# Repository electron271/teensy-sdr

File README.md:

# teensy-sdr
SDR (Software Defined Radio) using a Teensy development board.

## Libraries
https://github.com/XenGi/teensy_library
https://github.com/XenGi/teensy.pretty

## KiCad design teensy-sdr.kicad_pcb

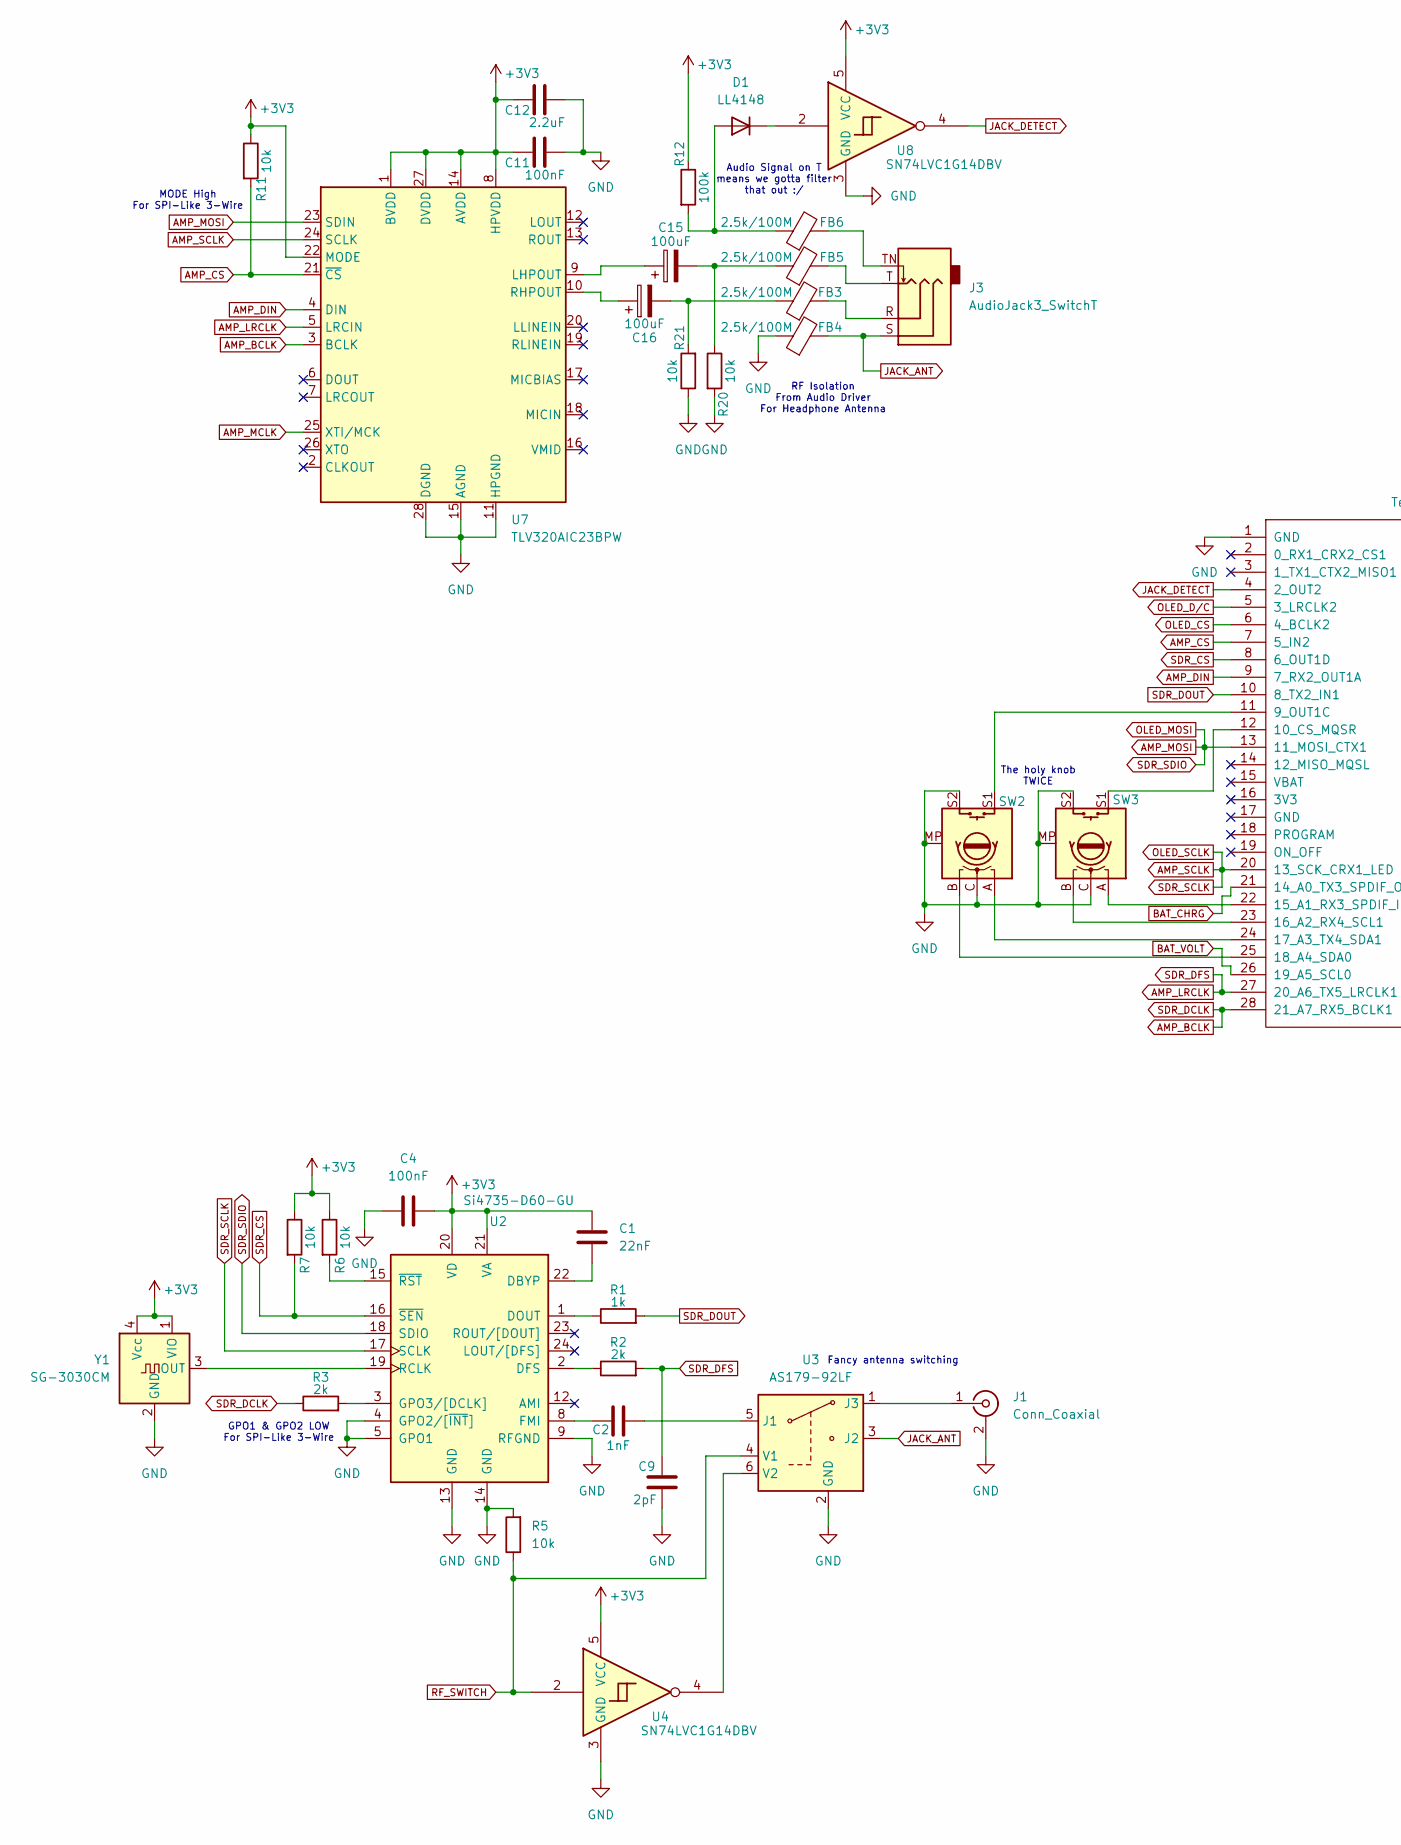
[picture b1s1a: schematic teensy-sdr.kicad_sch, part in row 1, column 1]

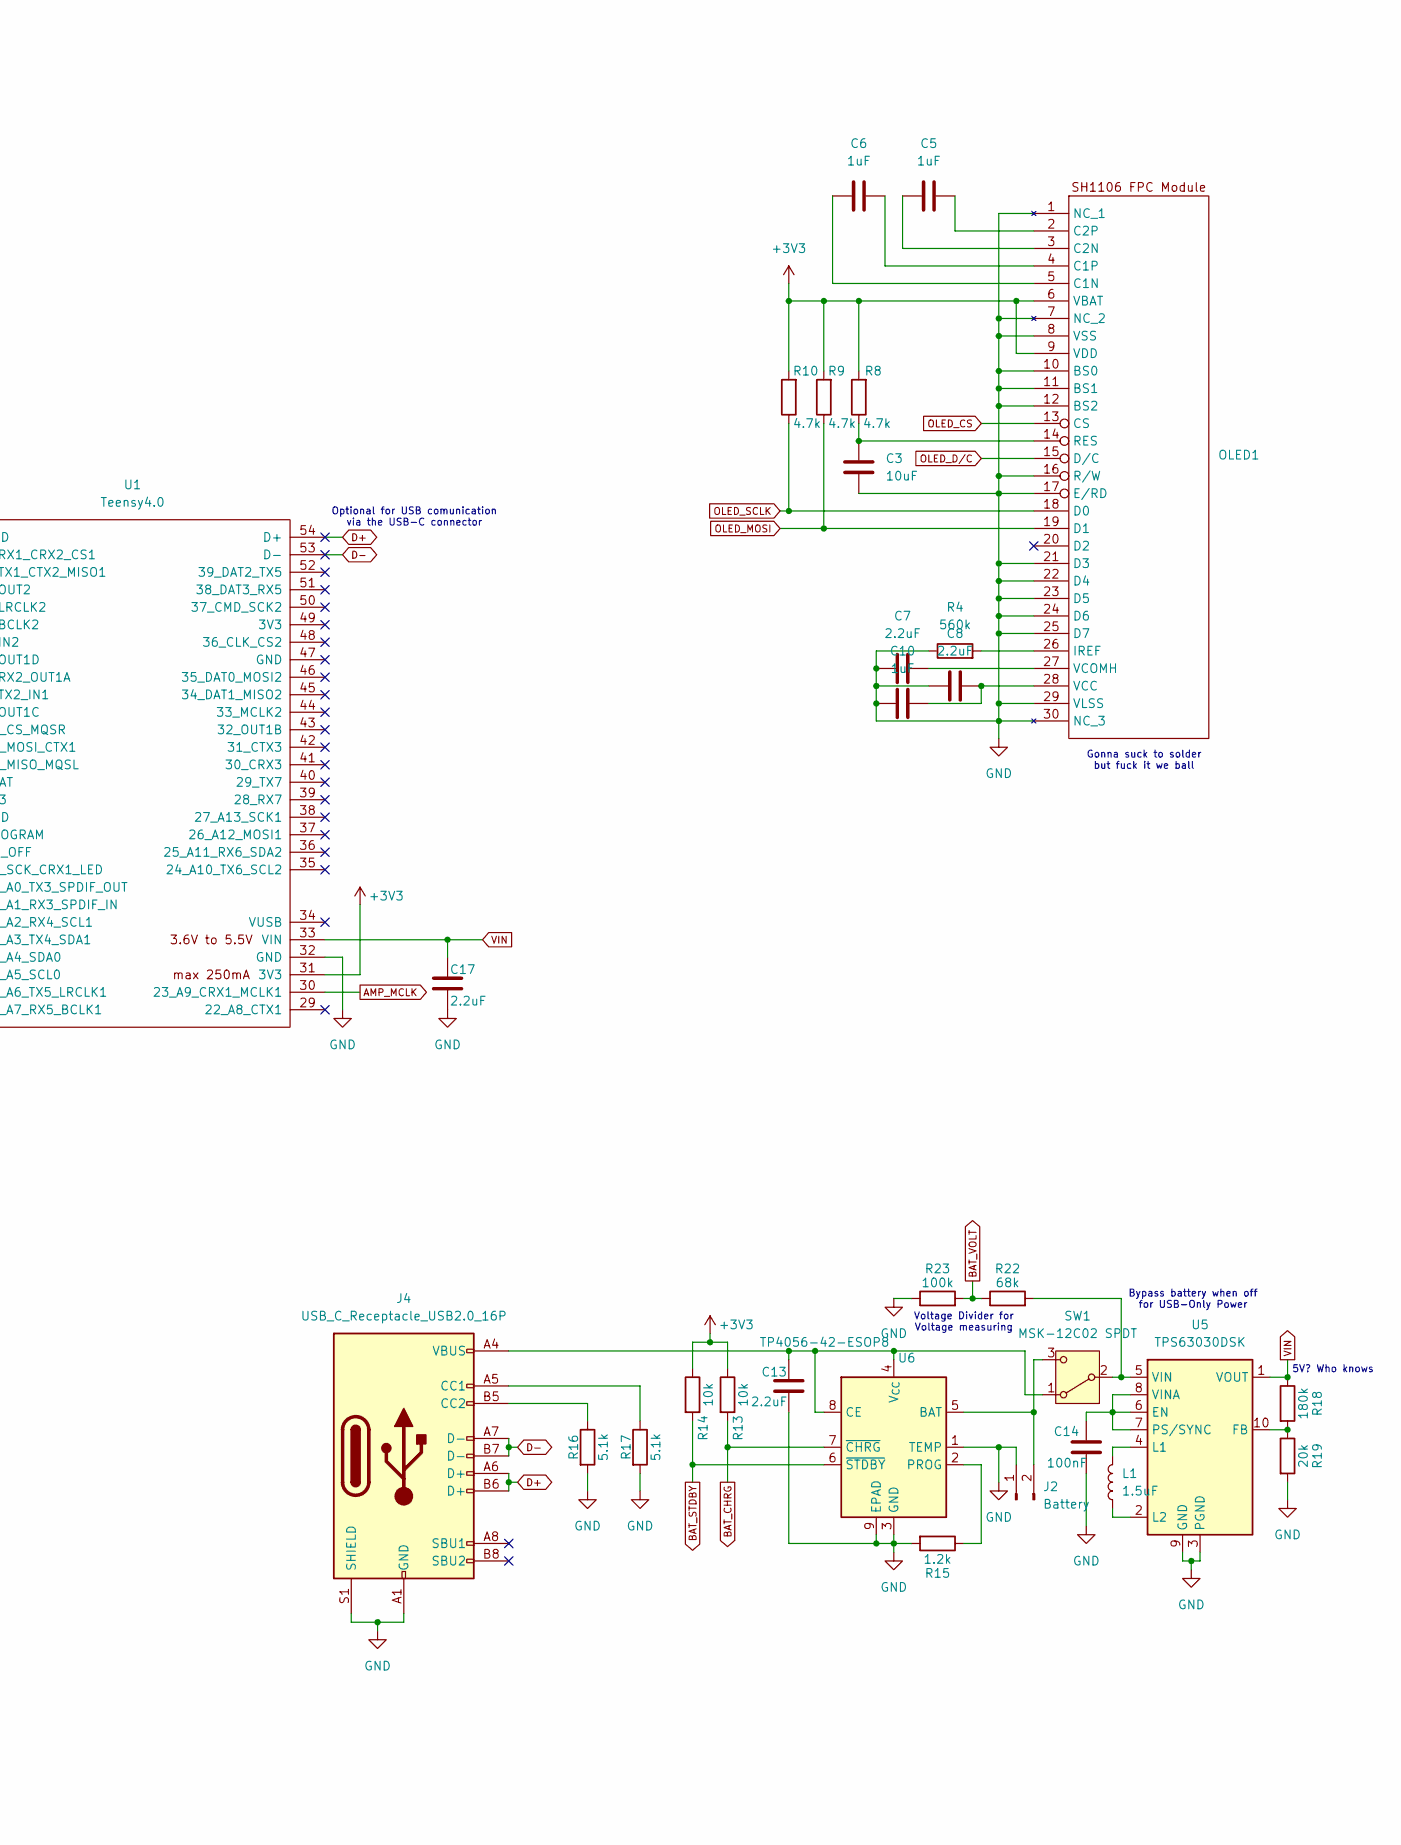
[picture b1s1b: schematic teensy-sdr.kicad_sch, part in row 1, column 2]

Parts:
C1: 22nF; C_0805_2012Metric_Pad1.18x1.45mm_HandSolder; LCSC C107147
C2: 1nF; C_0805_2012Metric_Pad1.18x1.45mm_HandSolder; LCSC C94121
C3: 10uF; C_0805_2012Metric_Pad1.18x1.45mm_HandSolder; LCSC C15850
C4, C11, C14: 100nF; C_0805_2012Metric_Pad1.18x1.45mm_HandSolder; LCSC C49678
C5, C6, C10: 1uF; C_0805_2012Metric_Pad1.18x1.45mm_HandSolder; LCSC C28323
C7, C8, C12, C13, C17: 2.2uF; C_0805_2012Metric_Pad1.18x1.45mm_HandSolder; LCSC C28234
C9: 2pF; C_0805_2012Metric_Pad1.18x1.45mm_HandSolder; LCSC C519932
C15, C16: 100uF; CP_Radial_D8.0mm_P3.50mm; LCSC C2990945
D1: LL4148; D_MiniMELF; LCSC C68883
FB3, FB4, FB5, FB6: 2.5k/100M; L_0805_2012Metric_Pad1.05x1.20mm_HandSolder; LCSC C394486
J1: Conn_Coaxial; SMA_Molex_73251-1153_EdgeMount_Horizontal; LCSC C5859238
J2: Battery; JST_PH_B2B-PH-K_1x02_P2.00mm_Vertical; LCSC C20088550
J3: AudioJack3_SwitchT; Jack_3.5mm_CUI_SJ-3524-SMT_Horizontal; LCSC C22359753
J4: USB_C_Receptacle_USB2.0_16P; USB_C_Receptacle_GCT_USB4105-xx-A_16P_TopMnt_Horizontal; LCSC C3025063
L1: 1.5uF; L_7.3x7.3_H3.5; LCSC C5189745
OLED1: Untitled
R1: 1k; R_0805_2012Metric_Pad1.20x1.40mm_HandSolder; LCSC C95781
R2, R3: 2k; R_0805_2012Metric_Pad1.20x1.40mm_HandSolder; LCSC C114572
R4: 560k; R_0805_2012Metric_Pad1.20x1.40mm_HandSolder; LCSC C865557
R5, R6, R7, R11, R13, R14, R20, R21: 10k; R_0805_2012Metric_Pad1.20x1.40mm_HandSolder; LCSC C84376
R8, R9, R10: 4.7k; R_0805_2012Metric_Pad1.20x1.40mm_HandSolder; LCSC C60816
R12, R23: 100k; R_0805_2012Metric_Pad1.20x1.40mm_HandSolder; LCSC C96346
R15: 1.2k; R_0805_2012Metric_Pad1.20x1.40mm_HandSolder; LCSC C114526
R16, R17: 5.1k; R_0805_2012Metric_Pad1.20x1.40mm_HandSolder; LCSC C2930296
R18: 180k; R_0805_2012Metric_Pad1.20x1.40mm_HandSolder; LCSC C17501
R19: 20k; R_0805_2012Metric_Pad1.20x1.40mm_HandSolder; LCSC C114566
R22: 68k; R_0805_2012Metric_Pad1.20x1.40mm_HandSolder; LCSC C17801
SW1: MSK-12C02 SPDT; SW_MSK12C02-HB; LCSC C431540
SW2, SW3: RotaryEncoder_Alps_EC11E-Switch_Vertical_H20mm_MountingHoles; LCSC C1322542
U1: Teensy4.0; Teensy40_SMT
U2: Si4735-D60-GU; SSOP-24_3.9x8.7mm_P0.635mm; LCSC C17686189
U3: AS179-92LF; SOT-363_SC-70-6; LCSC C83422
U4, U8: SN74LVC1G14DBV; SOT-23-5; LCSC C7835
U5: TPS63030DSK; WSON-10-1EP_2.5x2.5mm_P0.5mm_EP1.2x2mm; LCSC C12462
U6: TP4056-42-ESOP8; SOIC-8-1EP_3.9x4.9mm_P1.27mm_EP2.41x3.3mm_ThermalVias; LCSC C16581
U7: TLV320AIC23BPW; TSSOP-28_4.4x9.7mm_P0.65mm; LCSC C9915
Y1: SG-3030CM; Oscillator_SMD_SeikoEpson_SG3030CM; LCSC C21058396

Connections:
+3V3: C1.1, C4.2, C11.2, C12.2, OLED1.6 (VBAT), OLED1.9 (VDD), R6.1, R7.1, R8.2, R9.2, R10.2, R11.1, R12.1, R13.1, R14.1, U1.31 (3V3), U2.20 (VD), U2.21 (VA), U4.5 (VCC), U7.1 (BVDD), U7.8 (HPVDD), U7.14 (AVDD), U7.22 (MODE), U7.27 (DVDD), U8.5 (VCC), Y1.1 (VIO), Y1.4 (Vcc)
AMP_BCLK: R3.1, U1.28 (21_A7_RX5_BCLK1), U7.3 (BCLK)
AMP_CS: R11.2, U1.7 (5_IN2), U7.21 (~CS)
AMP_DIN: U1.9 (7_RX2_OUT1A), U7.4 (DIN)
AMP_LRCLK: C9.2, R2.2, U1.27 (20_A6_TX5_LRCLK1), U7.5 (LRCIN)
AMP_MCLK: U1.30 (23_A9_CRX1_MCLK1), U7.25 (XTI/MCK)
AMP_MOSI: OLED1.19 (D1), R9.1, U1.13 (11_MOSI_CTX1), U2.18 (SDIO), U7.23 (SDIN)
AMP_SCLK: OLED1.18 (D0), R10.1, U1.20 (13_SCK_CRX1_LED), U2.17 (SCLK), U7.24 (SCLK)
BAT_CHRG: R13.2, U1.21 (14_A0_TX3_SPDIF_OUT), U6.7 (~CHRG)
BAT_STDBY: R14.2, U6.6 (~STDBY)
BAT_VOLT: R22.1, R23.2, U1.26 (19_A5_SCL0)
D+: J4.A6 (D+), J4.B6 (D+), U1.54 (D+)
D-: J4.A7 (D-), J4.B7 (D-), U1.53 (D-)
GND: C3.1, C4.1, C7.1, C8.1, C9.1, C10.1, C11.1, C12.1, C13.2, C14.2, C17.2, FB4.1, J1.2 (Ext), J2.1, J4.A1 (GND), J4.A12 (GND), J4.B1 (GND), J4.B12 (GND), J4.S1 (SHIELD), OLED1.1 (NC_1), OLED1.7 (NC_2), OLED1.8 (VSS), OLED1.10 (BS0), OLED1.11 (BS1), OLED1.12 (BS2), OLED1.16 (R/W), OLED1.17 (E/RD), OLED1.21 (D3), OLED1.22 (D4), OLED1.23 (D5), OLED1.24 (D6), OLED1.25 (D7), OLED1.29 (VLSS), OLED1.30 (NC_3), R4.1, R5.2, R15.2, R16.2, R17.2, R19.2, R20.2, R21.1, R23.1, SW1.MP, SW2.C, SW2.MP, SW2.S2, SW3.C, SW3.MP, SW3.S2, U1.1 (GND), U1.32 (GND), U2.4 (GPO2/[~INT]), U2.5 (GPO1), U2.9 (RFGND), U2.13 (GND), U2.14 (GND), U3.2 (GND), U4.3 (GND), U5.3 (PGND), U5.9 (GND), U5.11 (PGND), U6.1 (TEMP), U6.3 (GND), U6.9 (EPAD), U7.11 (HPGND), U7.15 (AGND), U7.28 (DGND), U8.3 (GND), Y1.2 (GND)
JACK_ANT: FB4.2, J3.S, U3.3 (J2)
JACK_DETECT: U1.4 (2_OUT2), U8.4
unnamed: C15.2, FB5.1, R20.1
unnamed: C16.2, FB3.1, R21.2
unnamed: D1.2 (A), FB6.1, R12.2
unnamed: D1.1 (K), U8.2
unnamed: FB3.2, J3.R
unnamed: FB5.2, J3.T
unnamed: FB6.2, J3.TN
unnamed: J1.1 (In), U3.1 (J3)
unnamed: J2.2, SW1.3 (C), U6.5 (BAT)
unnamed: J4.A5 (CC1), R17.1
unnamed: J4.B5 (CC2), R16.1
unnamed: C6.1, OLED1.5 (C1N)
unnamed: C6.2, OLED1.4 (C1P)
unnamed: C5.1, OLED1.3 (C2N)
unnamed: C5.2, OLED1.2 (C2P)
unnamed: OLED1.26 (IREF), R4.2
unnamed: C3.2, OLED1.14 (RES), R8.1
unnamed: C8.2, C10.2, OLED1.28 (VCC)
unnamed: C7.2, OLED1.27 (VCOMH)
unnamed: C13.1, J4.A4 (VBUS), J4.A9 (VBUS), J4.B4 (VBUS), J4.B9 (VBUS), SW1.1 (A), U6.4 (V_{CC}), U6.8 (CE)
unnamed: R22.2, SW1.2 (B), U5.5 (VIN)
unnamed: SW2.S1, U1.11 (9_OUT1C)
unnamed: SW3.S1, U1.12 (10_CS_MQSR)
unnamed: SW3.A, U1.22 (15_A1_RX3_SPDIF_IN)
unnamed: SW3.B, U1.23 (16_A2_RX4_SCL1)
unnamed: SW2.A, U1.24 (17_A3_TX4_SDA1)
unnamed: SW2.B, U1.25 (18_A4_SDA0)
unnamed: C1.2, U2.22 (DBYP)
unnamed: R2.1, U2.2 (DFS)
unnamed: R1.1, U2.1 (DOUT)
unnamed: C2.1, U2.8 (FMI)
unnamed: R3.2, U2.3 (GPO3/[DCLK])
unnamed: U2.19 (RCLK), Y1.3 (OUT)
unnamed: R6.2, U2.15 (~RST)
unnamed: C2.2, U3.5 (J1)
unnamed: U3.6 (V2), U4.4
unnamed: C14.1, U5.6 (EN), U5.7 (PS/SYNC), U5.8 (VINA)
unnamed: R18.2, R19.1, U5.10 (FB)
unnamed: L1.2, U5.4 (L1)
unnamed: L1.1, U5.2 (L2)
unnamed: R15.1, U6.2 (PROG)
unnamed: C15.1, U7.9 (LHPOUT)
unnamed: C16.1, U7.10 (RHPOUT)
OLED_CS: OLED1.13 (CS), U1.6 (4_BCLK2)
OLED_D/C: OLED1.15 (D/C), U1.5 (3_LRCLK2)
RF_SWITCH: R5.1, U3.4 (V1), U4.2
SDR_CS: R7.2, U1.8 (6_OUT1D), U2.16 (~SEN)
SDR_DOUT: R1.2, U1.10 (8_TX2_IN1)
VIN: C17.1, R18.1, U1.33 (VIN), U5.1 (VOUT)

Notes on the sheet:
RF Isolation From Audio Driver For Headphone Antenna
Audio Signal on T means we gotta filter that out :/
Bypass battery when off for USB-Only Power
Voltage Divider for Voltage measuring
Fancy antenna switching
MODE High For SPI-Like 3-Wire
Gonna suck to solder but fuck it we ball
Optional for USB comunication via the USB-C connector
GPO1 & GPO2 LOW For SPI-Like 3-Wire
The holy knob TWICE
5V? Who knows

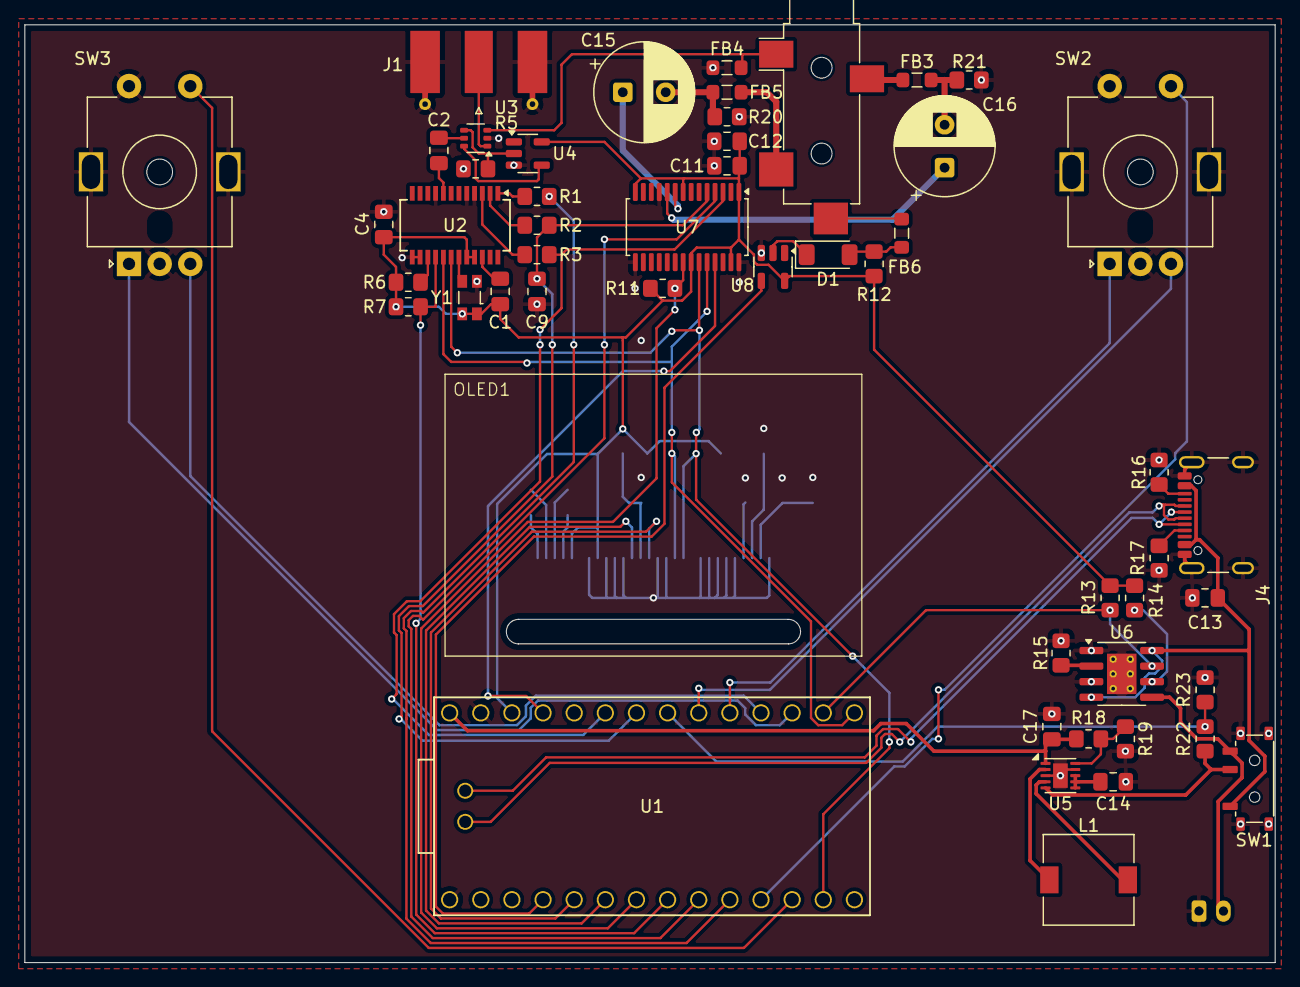
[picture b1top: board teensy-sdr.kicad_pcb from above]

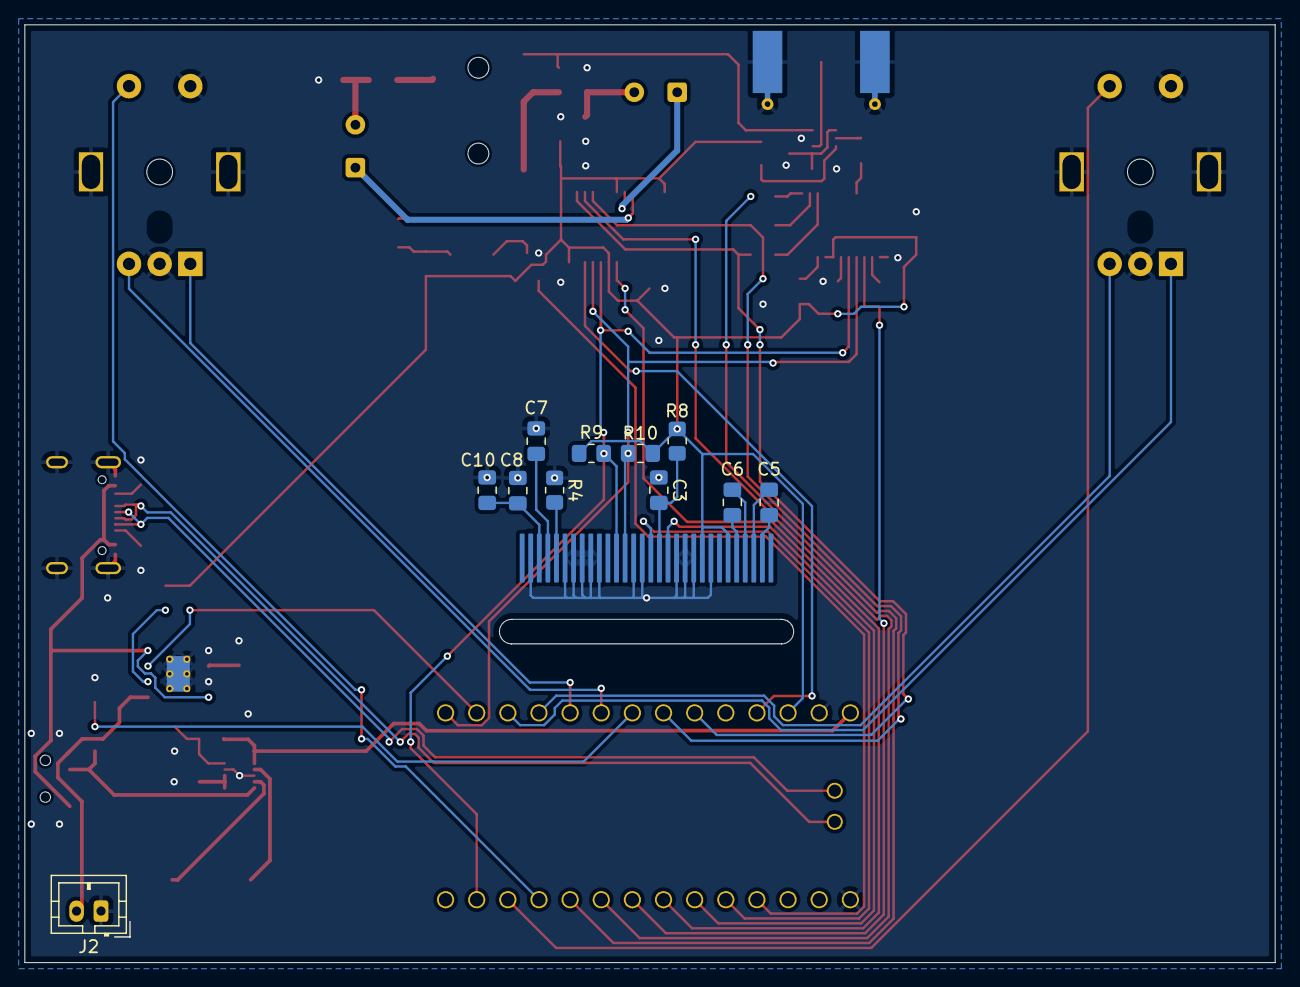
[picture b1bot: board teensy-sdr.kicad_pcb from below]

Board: 2 copper layers, 102.0 x 76.5 mm, 63 parts (11 on the bottom side), 65 nets.

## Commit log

2025-05-27 init
2025-05-27 libraries
2025-05-28 idk what i am doin
2025-05-28 fix lock file
2025-05-30 PCB Refractor
2025-05-30 remove graphics
2025-05-31 fix gitignore
2025-05-31 fix swapped I2S lines
